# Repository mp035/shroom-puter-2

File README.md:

# shroom-puter-2
A climate control device to regulate air flow, temperature, humidity and lighting cycles in a repurposed refridgerator for growing mushrooms and other cultures.

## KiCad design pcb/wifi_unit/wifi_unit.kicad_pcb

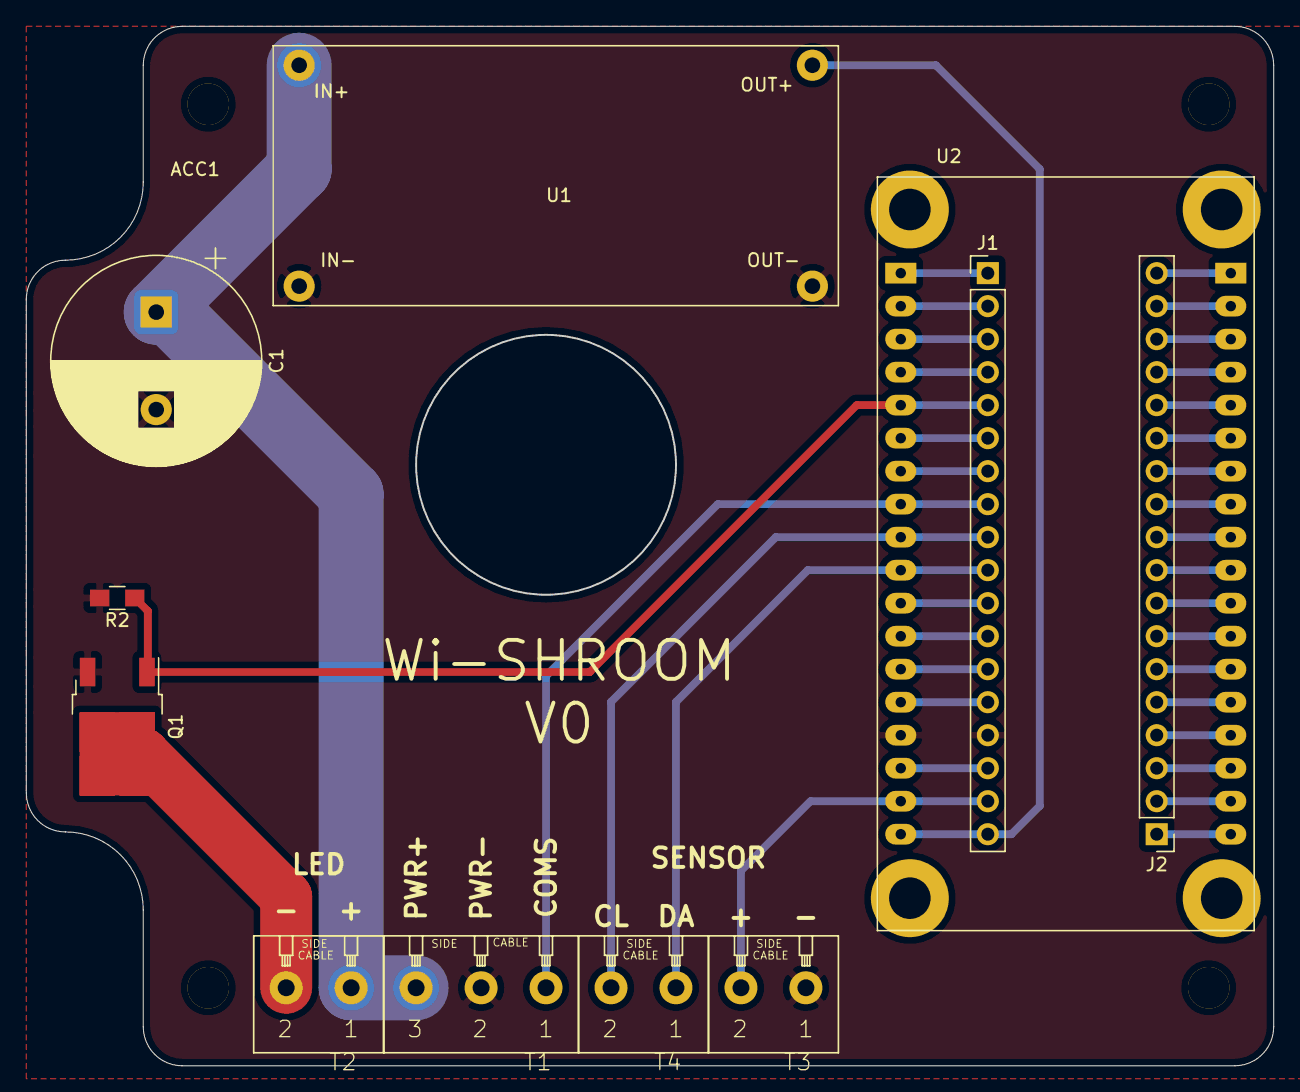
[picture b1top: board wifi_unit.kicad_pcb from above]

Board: 2 copper layers, 96.0 x 80.0 mm, 12 parts (0 on the bottom side), 38 nets.

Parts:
ACC1: ACCESSORY_NO_PINS; electus_hb6217
C1: 4700uf 25v; CP_Radial_D16.0mm_P7.50mm
J1, J2: Conn_01x18; PinHeader_1x18_P2.54mm_Vertical
Q1: NVD6828NLT4G; TO-252-2
R2: 100K; R_0805_HandSoldering
T1: TERMINAL_ELEMENT14_5MM_X3
T2, T3, T4: TERMINAL_ELEMENT14_5MM_X2
U1: REGULATOR_MODULE; LM2596_SW_REG
U2: firebeetle_esp32

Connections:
+3V3: J1.17, T3.2, U2.17
+5V: J1.18, U1.4, U2.18
/COMMS: J1.8, T1.1, U2.8
/LIGHT: J1.5, Q1.1, R2.1, U2.5
/SENSOR_SCL: J1.9, T4.2, U2.9
/SENSOR_SDA: J1.10, T4.1, U2.10
GND: C1.2, J1.15, Q1.3, R2.2, T1.2, T3.1, U1.2, U1.3, U2.15
unnamed: J1.1, U2.1
unnamed: J1.2, U2.2
unnamed: J1.3, U2.3
unnamed: J1.4, U2.4
unnamed: J1.6, U2.6
unnamed: J1.7, U2.7
unnamed: J1.11, U2.11
unnamed: J1.12, U2.12
unnamed: J1.13, U2.13
unnamed: J1.14, U2.14
unnamed: J1.16, U2.16
unnamed: J2.1, U2.19
unnamed: J2.2, U2.20
unnamed: J2.3, U2.21
unnamed: J2.4, U2.22
unnamed: J2.5, U2.23
unnamed: J2.6, U2.24
unnamed: J2.7, U2.25
unnamed: J2.8, U2.26
unnamed: J2.9, U2.27
unnamed: J2.10, U2.28
unnamed: J2.11, U2.29
unnamed: J2.12, U2.30
unnamed: J2.13, U2.31
unnamed: J2.14, U2.32
unnamed: J2.15, U2.33
unnamed: J2.16, U2.34
unnamed: J2.17, U2.35
unnamed: J2.18, U2.36
unnamed: Q1.2, T2.2
VDD: C1.1, T1.3, T2.1, U1.1

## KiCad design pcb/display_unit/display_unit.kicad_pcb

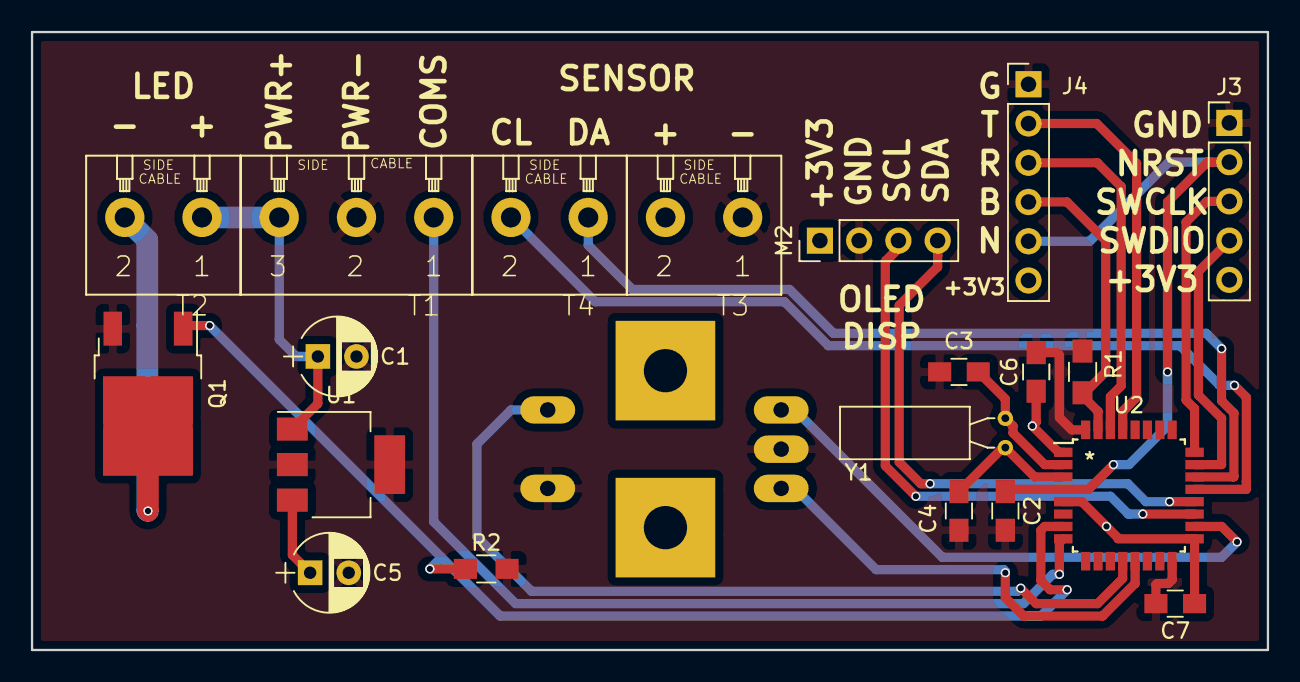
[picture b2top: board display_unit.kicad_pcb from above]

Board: 2 copper layers, 80.0 x 40.0 mm, 21 parts (1 on the bottom side), 21 nets.

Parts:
C1: 10uf 25v; CP_Radial_D5.0mm_P2.50mm
C2, C6, C7: 100nf; C_0805_HandSoldering
C3, C4: 22pf; C_0805_HandSoldering
C5: 10uf 6.3v; CP_Radial_D5.0mm_P2.50mm
J3: Conn_01x05; Pin_Header_Straight_1x05_Pitch2.54mm
J4: Conn_01x06; Pin_Header_Straight_1x06_Pitch2.54mm
M1: ROTARY-ENCODER
M2: 096_INCH_OLED; Pin_Header_Straight_1x04_Pitch2.54mm
Q1: NVD6828NLT4G; TO-252-2
R1: 10K; R_0805_HandSoldering
R2: 100K; R_0805_HandSoldering
T1: TERMINAL_ELEMENT14_5MM_X3
T2, T3, T4: TERMINAL_ELEMENT14_5MM_X2
U1: UA78M33CDCY; SOT-223-3_TabPin2
U2: STM32L031K6Tx; LQFP-32_7x7mm_Pitch0.8mm
Y1: Crystal; Crystal_C38-LF_d3.0mm_l8.0mm_Horizontal

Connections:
+3V3: C5.1, C6.1, C7.1, J3.5, J4.6, M2.1, T3.P$2, U1.3, U2.1, U2.5, U2.17
/BOOT0: J4.4, R1.1, U2.31
/COMMS: T1.P$1, U2.8
/ENC_PB: M1.P5, U2.12
/ENC_R1: M1.P3, U2.18
/ENC_R2: M1.P1, U2.13
/LIGHT: Q1.1, R2.1, U2.7
/MCU_RX: J4.3, U2.30
/MCU_TX: J4.2, U2.29
/NRST: C2.1, J3.2, J4.5, U2.4
/OLED_SCL: M2.3, U2.19
/OLED_SDA: M2.4, U2.20
/SENSOR_SCL: T4.P$2, U2.21
/SENSOR_SDA: T4.P$1, U2.22
/SWCLK: J3.3, U2.24
/SWDIO: J3.4, U2.23
GND: C1.2, C2.2, C3.2, C4.2, C5.2, C6.2, C7.2, J3.1, J4.1, M1.P2, M1.P4, M2.2, Q1.3, R1.2, R2.2, T1.P$2, T3.P$1, U1.2, U2.16, U2.32
unnamed: C3.1, U2.2, Y1.1
unnamed: C4.1, U2.3, Y1.2
unnamed: Q1.2, T2.P$2
VDD: C1.1, T1.P$3, T2.P$1, U1.1

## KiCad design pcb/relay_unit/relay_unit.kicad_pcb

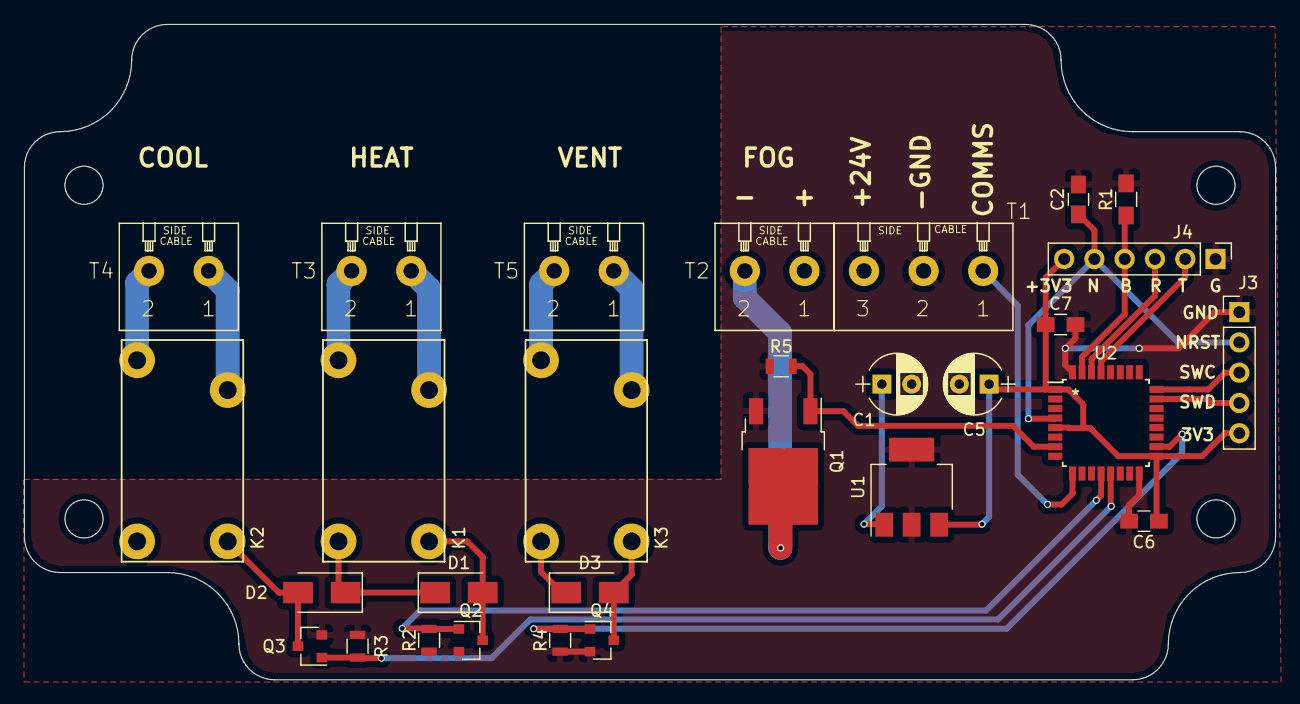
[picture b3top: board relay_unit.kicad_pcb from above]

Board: 2 copper layers, 105.0 x 55.0 mm, 29 parts (0 on the bottom side), 24 nets.

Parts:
C1, C5: CP; CP_Radial_D5.0mm_P2.50mm
C2, C6, C7: 100nf; C_0805_HandSoldering
D1, D2, D3: S1M; D_SMA
J3: Conn_01x05; Pin_Header_Straight_1x05_Pitch2.54mm
J4: Conn_01x06; Pin_Header_Straight_1x06_Pitch2.54mm
K1, K2, K3: TE_OJ_Series; OJ-SS
Q1: NVD6828NLT4G; TO-252-2
Q2, Q3, Q4: 2N7002; SOT-23
R1: 10K; R_0805_HandSoldering
R2, R3, R4, R5: 100K; R_0805
T1: TERMINAL_ELEMENT14_5MM_X3
T2, T3, T4, T5: TERMINAL_ELEMENT14_5MM_X2
U1: UA78M33CDCY; SOT-223-3_TabPin2
U2: STM32L031K6Tx; LQFP-32_7x7mm_Pitch0.8mm

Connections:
+3V3: C5.1, C6.1, C7.1, J3.5, J4.6, U1.3, U2.1, U2.5, U2.17
+24V: C1.1, D1.1, D2.1, D3.1, K1.5, K2.5, K3.5, T1.P$3, T2.P$1, U1.1
/BOOT0: J4.4, R1.1, U2.31
/COMMS: T1.P$1, U2.9
/COOL: Q3.1, R3.2, U2.13
/FOGGER: Q1.1, R5.2, U2.7
/HEAT: Q2.1, R2.2, U2.12
/MCU_RX: J4.3, U2.30
/MCU_TX: J4.2, U2.29
/NRST: C2.1, J3.2, J4.5, U2.4
/SWCLK: J3.3, U2.24
/SWDIO: J3.4, U2.23
/VENT: Q4.1, R4.2, U2.18
GND: C1.2, C2.2, C5.2, C6.2, C7.2, J3.1, J4.1, Q1.3, Q2.2, Q3.2, Q4.2, R1.2, R2.1, R3.1, R4.1, R5.1, T1.P$2, U1.2, U2.16, U2.32
unnamed: D1.2, K1.1, Q2.3
unnamed: D2.2, K2.1, Q3.3
unnamed: D3.2, K3.1, Q4.3
unnamed: K1.2, T3.P$1
unnamed: K1.3, T3.P$2
unnamed: K2.2, T4.P$1
unnamed: K2.3, T4.P$2
unnamed: K3.2, T5.P$1
unnamed: K3.3, T5.P$2
unnamed: Q1.2, T2.P$2

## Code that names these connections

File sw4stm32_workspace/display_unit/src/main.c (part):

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			

static const uint8_t water[34] = {16,16,     0,0,0,0,0,192,240,248,254,240,192,0,0,0,0,0,0,0,0,0,31,63,127,127,127,112,57,31,0,0,0,0,};
static const uint8_t cool[34] = {16,16,     0,72,140,16,96,164,72,126,72,164,96,16,140,72,0,0,1,37,99,17,13,75,36,252,36,75,13,17,99,37,1,0,};
static const uint8_t light_on[34] = {16,16,    0,0,0,112,140,2,33,65,33,65,33,2,140,112,0,0,0,0,0,0,1,2,126,213,212,213,126,2,1,0,0,0,};
static const uint8_t fan[34] = {16,16,    0,0,240,12,198,194,217,93,61,193,194,198,12,240,0,0,0,0,0,131,134,133,137,248,248,137,133,134,131,0,0,0,};
static const uint8_t heat[34] = {16,16,    0,128,130,4,192,240,240,248,251,248,240,240,192,4,130,128,0,0,32,16,1,7,7,15,111,15,7,7,1,16,32,0,};
static const uint8_t light_off[34] = {16,16,    0,0,0,248,204,2,3,129,193,225,115,58,158,254,7,3,0,96,112,56,31,14,127,243,241,240,124,14,3,0,0,0,};
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	const char* enableRh = "ENABLE R/H    ";
	const char* disableRh = "DISABLE R/H   ";

	const char* enableLight = "ENABLE LIGHT  ";
	const char* disableLight = "DISABLE LIGHT ";

	const char* enableVent = "ENABLE VENT   ";
	const char* disableVent = "DISABLE VENT  ";

	menuItem_t disableMenuItems[]={
			{"GO BACK       ", APPL_MENU, &mainMenu},
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
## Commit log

2017-10-30 Display PCB schematic finished.
2017-10-31 Layed out display PCB.
2017-11-01 laid out relay board.
2017-11-06 Added pull down resistor on led light driver
2017-11-06 Generated V0 gerbers.
2017-12-01 Got oled working.
2017-12-01 Moved sw4stm32_workspace and removed old git repository.
2017-12-03 Got UI working on display unit.
2017-12-05 Added relay unit code. Should be ready to test.
2017-12-06 Finished firmware.
2017-12-06 Attempted to fix bad load value for temperature save.
2018-11-24 Fixed rotary encoder. Added function to start vent when humidifier runs.
2018-11-24 Re-added humidity bandwidth system.
2021-11-22 added wifi unit pcb
2021-11-22 Merged files.
